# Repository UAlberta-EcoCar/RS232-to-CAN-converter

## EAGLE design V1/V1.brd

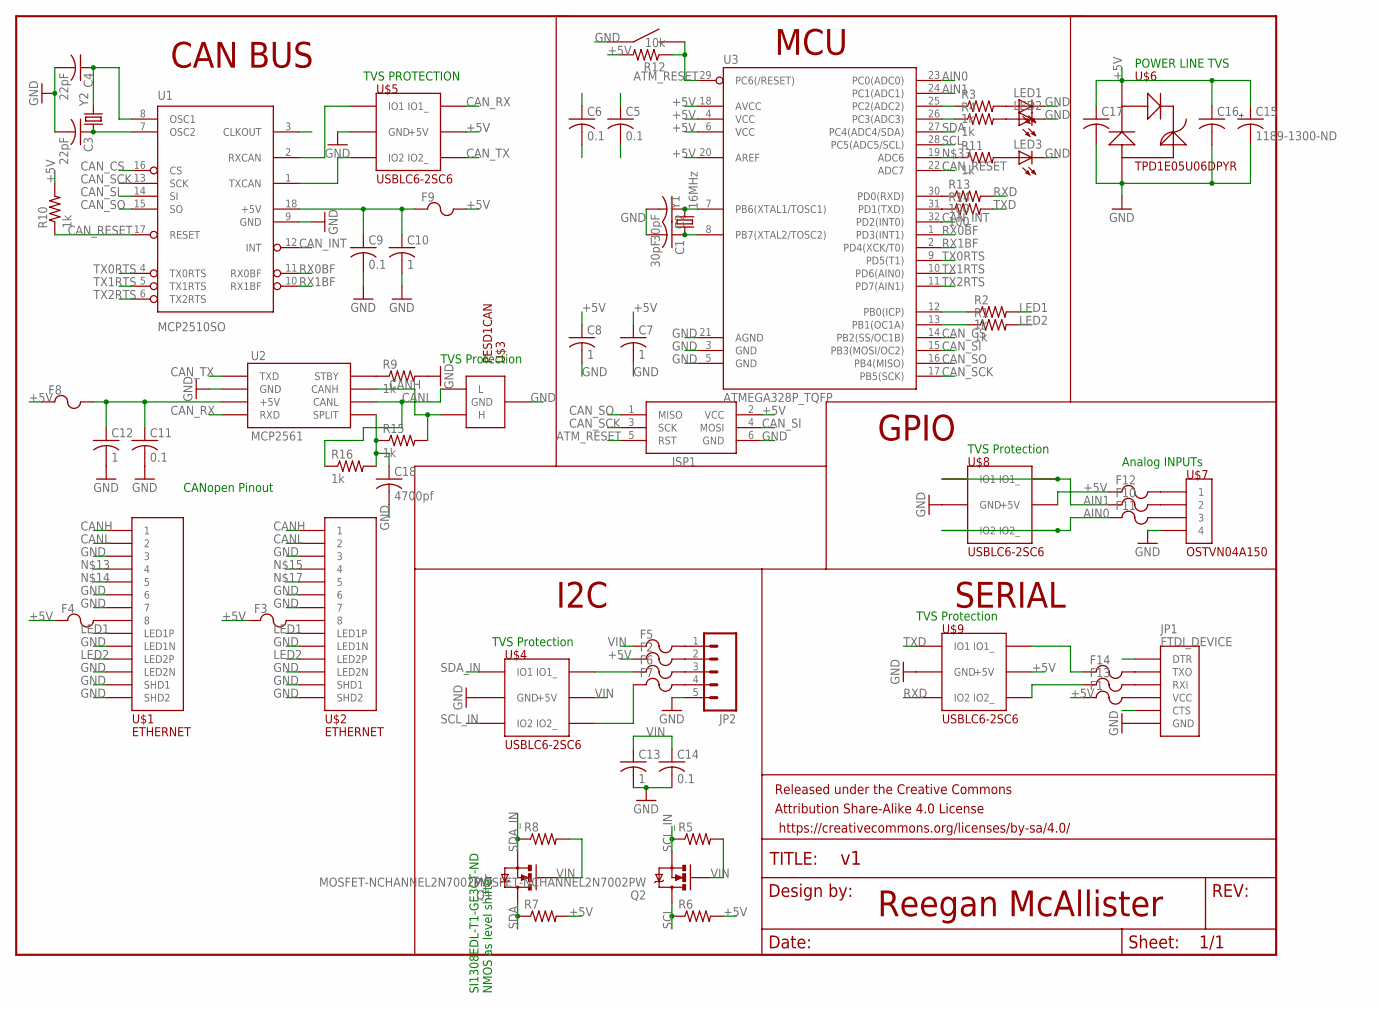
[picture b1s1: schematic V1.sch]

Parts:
C1, C2: 30pF; C0603K
C3, C4: 22pF; C0603K
C5, C6, C9, C11, C14: 0.1; C0603K
C7, C8, C10, C12, C13: 1; C0603K
C15: 1189-1300-ND
C16, C17: C-USC0603K; C0603K
C18: 4700pf; C0603K
F1, F2, F3, F4, F5, F6, F7, F8, F9, F10, F11, F12, F13, F14: POLYFUSE; 1206
FRAME1: FRAME-LETTERNO_PACKAGE; DUMMY
ISP1: AVRISP-BOX
JP1: FTDI_DEVICE; FTDI_DEVICE_SIDE
JP2: M05NO_SILK; 1X05_NO_SILK
LED1, LED2, LED3: LEDCHIPLED_0805; CHIPLED_0805
Q1, Q2: MOSFET-NCHANNEL2N7002PW; SOT323
R1, R2, R3, R4, R9, R10, R11, R15, R16: 1k; 0603-RES
R5, R6, R7, R8: RESISTOR0603-RES; 0603-RES
R12: 10k; 0603-RES
R13, R14: 100; 0603-RES
U1: MCP2510SO; SO-18W
U2: MCP2561; DIP8
U3: ATMEGA328P_TQFP; TQFP32-08
U$1, U$2: ETHERNET; A122645-ND
U$3: PESD1CAN
U$4, U$5, U$8, U$9: USBLC6-2SC6
U$6: TPD1E05U06DPYR; 2-XDFN
U$7: OSTVN04A150; OSTVN04A1450
U$10: EG4621CT-ND
Y1: 16MHz; HC49US
Y2: CRYSTALHC49US; HC49US

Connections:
+5V: C5.1, C6.1, C7.1, C8.1, C15.P$2 (+), C16.1, C17.1, F1.1, F2.1, F3.1, F4.1, F8.1, F9.2, F12.1, ISP1.2 (VCC), R6.2, R7.2, R10.2, R12.2, U3.4 (VCC), U3.6 (VCC), U3.18 (AVCC), U3.20 (AREF), U$5.P$5 (+5V), U$6.P$1, U$8.P$5 (+5V), U$9.P$5 (+5V)
AIN0: F11.1, U3.23 (PC0(ADC0)), U$8.P$3 (IO2), U$8.P$4 (IO2_)
AIN1: F10.1, U3.24 (PC1(ADC1)), U$8.P$1 (IO1), U$8.P$6 (IO1_)
ATM_RESET: ISP1.5 (RST), R12.1, U3.29 (PC6(/RESET)), U$10.P$3, U$10.P$4
CANH: R15.2, U2.P$7 (CANH), U$1.P$1 (1), U$2.P$1 (1), U$3.P$1 (H)
CANL: R16.1, U2.P$6 (CANL), U$1.P$2 (2), U$2.P$2 (2), U$3.P$2 (L)
CAN_CS: U1.16 (CS), U3.14 (PB2(SS/OC1B))
CAN_INT: U1.12 (INT), U3.32 (PD2(INT0))
CAN_RESET: R10.1, U1.17 (RESET), U3.22 (ADC7)
CAN_RX: U2.P$4 (RXD), U$5.P$6 (IO1_)
CAN_SCK: ISP1.3 (SCK), U1.13 (SCK), U3.17 (PB5(SCK))
CAN_SI: ISP1.4 (MOSI), U1.14 (SI), U3.15 (PB3(MOSI/OC2))
CAN_SO: ISP1.1 (MISO), U1.15 (SO), U3.16 (PB4(MISO))
CAN_TX: U2.P$1 (TXD), U$5.P$4 (IO2_)
GND: C1.2, C2.2, C3.2, C4.2, C5.2, C6.2, C7.2, C8.2, C9.2, C10.2, C11.2, C12.2, C13.2, C14.2, C15.P$1 (-), C16.2, C17.2, C18.2, ISP1.6 (GND), JP1.P$6 (GND), JP2.5, LED1.C, LED2.C, LED3.C, R9.2, U1.9 (GND), U2.P$2 (GND), U3.3 (GND), U3.5 (GND), U3.21 (AGND), U$1.P$3 (3), U$1.P$6 (6), U$1.P$7 (7), U$1.P$9 (LED1N), U$1.P$11 (LED2N), U$1.P$13 (SHD1), U$1.P$14 (SHD2), U$2.P$3 (3), U$2.P$6 (6), U$2.P$7 (7), U$2.P$9 (LED1N), U$2.P$11 (LED2N), U$2.P$13 (SHD1), U$2.P$14 (SHD2), U$3.P$3 (GND), U$4.P$2 (GND), U$5.P$2 (GND), U$6.P$2, U$7.P$4 (4), U$8.P$2 (GND), U$9.P$2 (GND), U$10.P$1, U$10.P$2
LED1: R2.2, U$1.P$10 (LED1P), U$2.P$10 (LED1P)
LED2: R1.2, U$1.P$12 (LED2P), U$2.P$12 (LED2P)
unnamed: F3.2, U$2.P$8 (8)
unnamed: R1.1, U3.13 (PB1(OC1A))
unnamed: R3.1, U3.25 (PC2(ADC2))
unnamed: R2.1, U3.12 (PB0(ICP))
unnamed: C4.1, U1.8 (OSC1), Y2.2
unnamed: C3.1, U1.7 (OSC2), Y2.1
unnamed: C2.1, U3.7 (PB6(XTAL1/TOSC1)), Y1.2
unnamed: C1.1, U3.8 (PB7(XTAL2/TOSC2)), Y1.1
unnamed: F10.2, U$7.P$2 (2)
unnamed: F11.2, U$7.P$3 (3)
unnamed: LED1.A, R3.2
unnamed: LED2.A, R4.2
unnamed: F1.2, JP1.P$4 (VCC)
unnamed: F2.2, JP2.2
unnamed: F4.2, U$1.P$8 (8)
unnamed: F5.2, JP2.1
unnamed: F6.2, JP2.3
unnamed: F7.2, JP2.4
unnamed: F6.1, U$4.P$6 (IO1_)
unnamed: F7.1, U$4.P$4 (IO2_)
unnamed: C11.1, C12.1, F8.2, U2.P$3 (+5V)
unnamed: C9.1, C10.1, F9.1, U1.18 (+5V)
unnamed: U1.1 (TXCAN), U$5.P$3 (IO2)
unnamed: U1.2 (RXCAN), U$5.P$1 (IO1)
unnamed: R11.1, U3.19 (ADC6)
unnamed: F12.2, U$7.P$1 (1)
unnamed: R9.1, U2.P$8 (STBY)
unnamed: R4.1, U3.26 (PC3(ADC3))
unnamed: LED3.A, R11.2
unnamed: R13.1, U3.30 (PD0(RXD))
unnamed: R14.1, U3.31 (PD1(TXD))
unnamed: F13.2, JP1.P$3 (RXI)
unnamed: F14.2, JP1.P$2 (TXO)
unnamed: F14.1, U$9.P$6 (IO1_)
unnamed: F13.1, U$9.P$4 (IO2_)
unnamed: C18.1, R15.1, R16.2, U2.P$5 (SPLIT)
RX0BF: U1.11 (RX0BF), U3.1 (PD3(INT1))
RX1BF: U1.10 (RX1BF), U3.2 (PD4(XCK/T0))
RXD: R13.2, U$9.P$3 (IO2)
SCL: Q2.3 (D), R6.1, U3.28 (PC5(ADC5/SCL))
SCL_IN: Q2.2 (S), R5.1, U$4.P$3 (IO2)
SDA: Q1.3 (D), R7.1, U3.27 (PC4(ADC4/SDA))
SDA_IN: Q1.2 (S), R8.1, U$4.P$1 (IO1)
TX0RTS: U1.4 (TX0RTS), U3.9 (PD5(T1))
TX1RTS: U1.5 (TX1RTS), U3.10 (PD6(AIN0))
TX2RTS: U1.6 (TX2RTS), U3.11 (PD7(AIN1))
TXD: R14.2, U$9.P$1 (IO1)
VIN: C13.1, C14.1, F5.1, Q1.1 (G), Q2.1 (G), R5.2, R8.2, U$4.P$5 (+5V)

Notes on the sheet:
CANopen Pinout
TVS Protection
TVS PROTECTION
SI1308EDL-T1-GE3CT-ND NMOS as level shifter
POWER LINE TVS
Analog INPUTs
CAN BUS
I2C
MCU
SERIAL
Reegan McAllister
GPIO

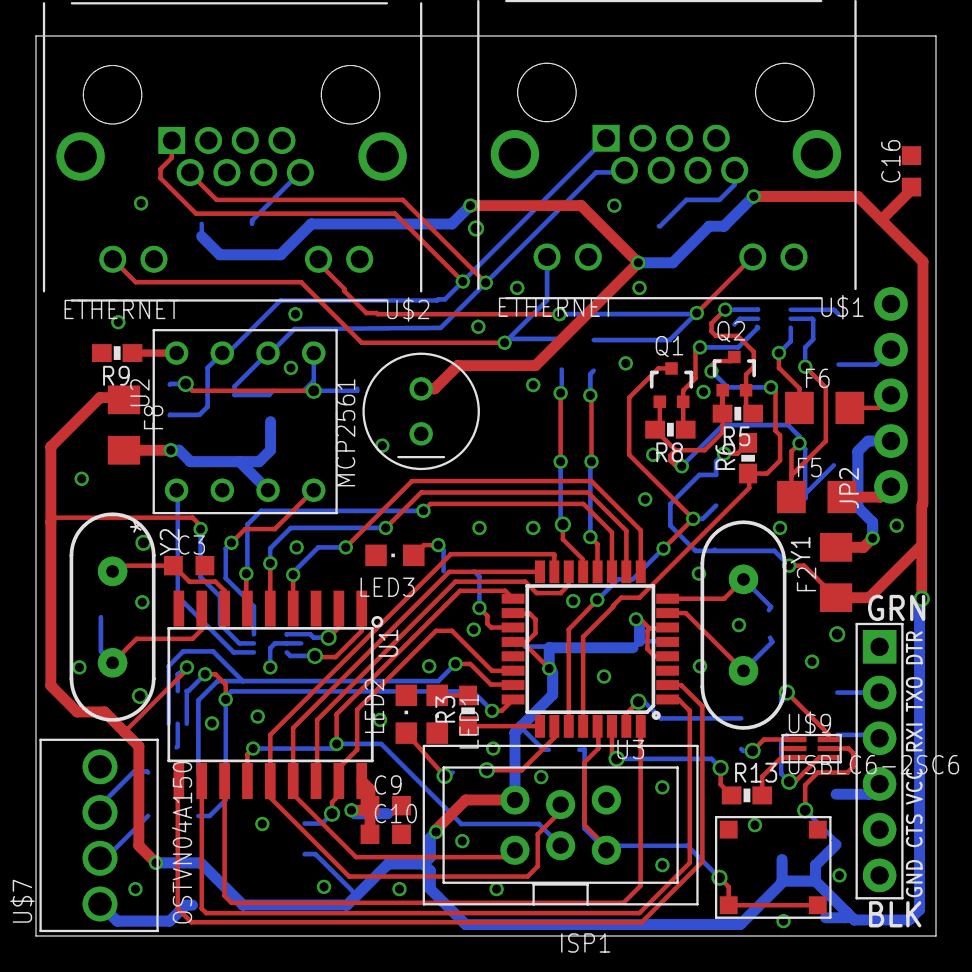
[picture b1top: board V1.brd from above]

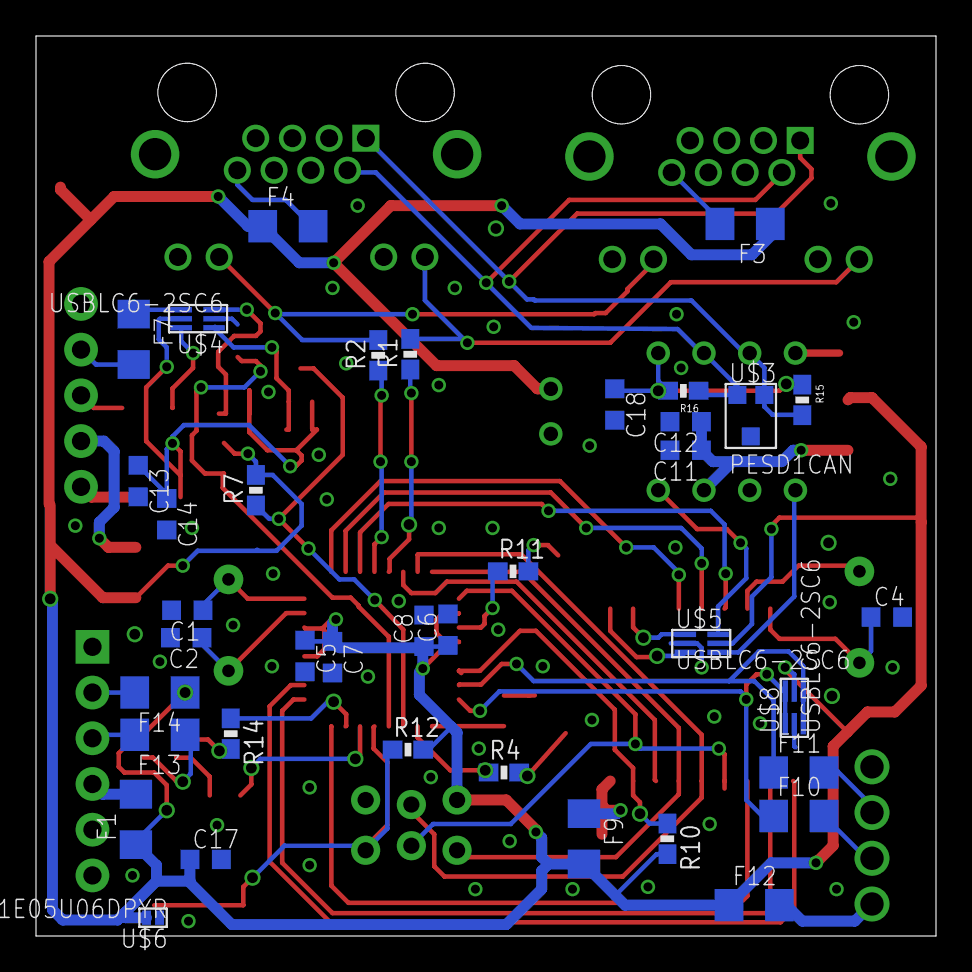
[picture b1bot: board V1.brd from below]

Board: 2 copper layers, 50.0 x 50.0 mm, 72 parts (38 on the bottom side), 65 nets.

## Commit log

2016-09-13 :octocat: Added .gitattributes & .gitignore files
2016-09-13 Create LICENSE
2016-09-28 CHanged cap values on MCP2515 to 22pF
2016-12-28 moved everything into folders, started coding

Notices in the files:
parts and their libraries:
SparkFun-Aesthetics: Licensing: Creative Commons ShareAlike 4.0 International - https://creativecommons.org/licenses/by-sa/4.0
SparkFun-Aesthetics: Released under the Creative Commons Attribution Share-Alike 4.0 License
SparkFun-Aesthetics: https://creativecommons.org/licenses/by-sa/4.0
